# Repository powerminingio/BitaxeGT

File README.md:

# Bitaxe Gamma Turbo

Bitaxe Gamma Turbo is a dual BM1370 Open Source Bitcoin miner using [esp-miner](https://github.com/bitaxeorg/esp-miner). This project aims to provide a high-performance, energy-efficient Bitcoin mining solution using modern ASIC hardware.

## Version

The first release of the Bitaxe Gamma Turbo (GT) marks the version 801.

Major improvements over the version 800xxx are changes in the selected components and refitting components and headers on the PCB.

## Features

- Dual BM1370 ASIC
- Dual TPS546*
- Improved Mounting Hole selection
- 12V BAP
- EMC2103

The Bitaxe Gamma Turbo is the first iteration of a dual ASIC chip variant and marks the first point of multi-chip devices with modern ASIC hardware.

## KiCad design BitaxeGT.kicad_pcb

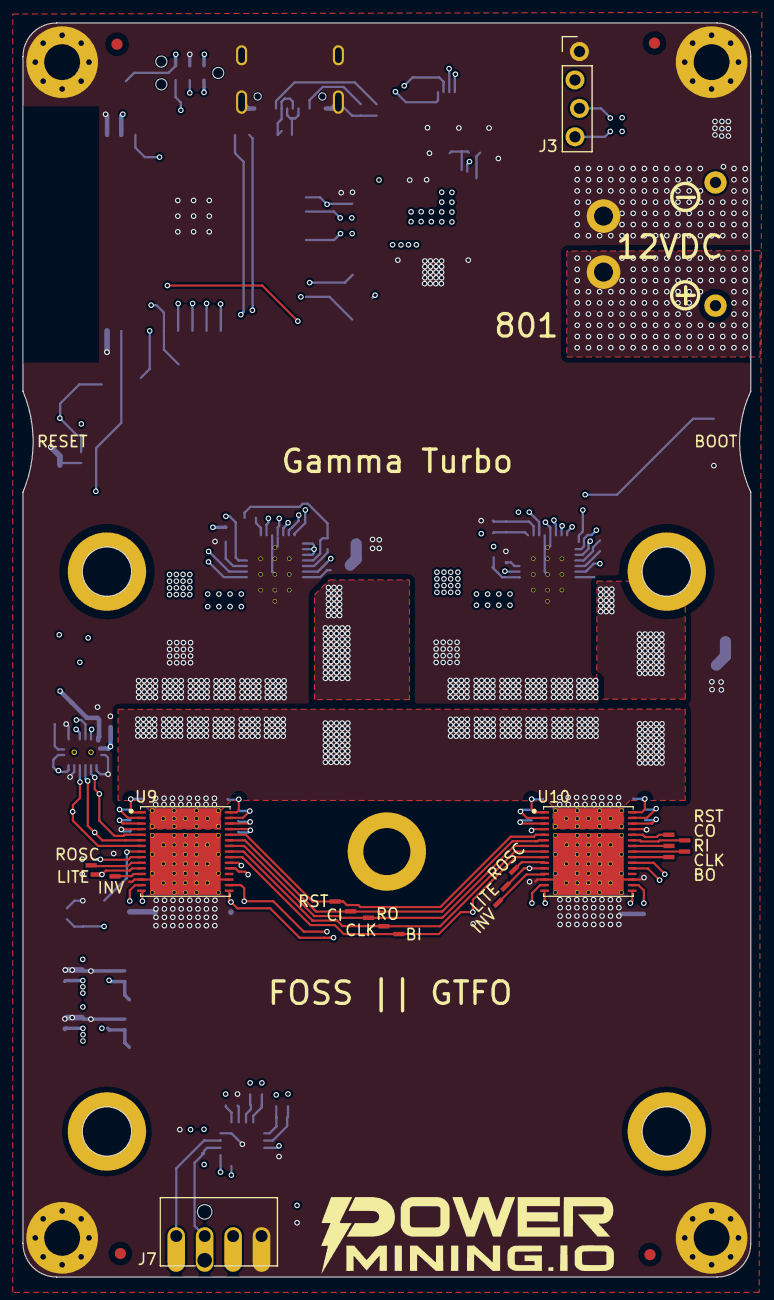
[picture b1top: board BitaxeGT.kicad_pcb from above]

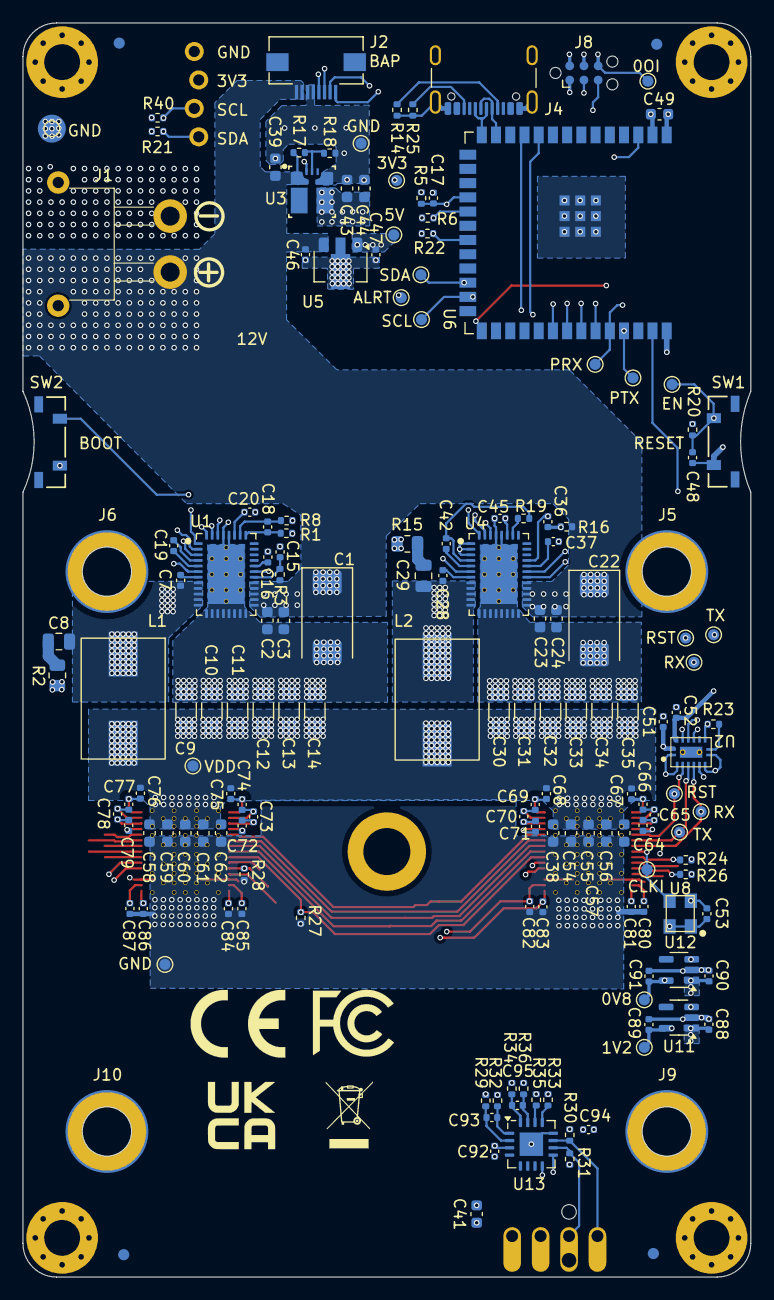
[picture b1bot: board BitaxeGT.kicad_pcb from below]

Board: 6 copper layers, 65.0 x 112.0 mm, 191 parts (163 on the bottom side), 98 nets.

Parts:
C1, C22: 33uF; CP_EIA-7343-31_Kemet-D
C2, C3, C23, C24, C38, C39, C41, C43, C44, C49, C54, C55, C56, C57, C58, C59, C60, C61, C62: 10uF; C_0603_1608Metric
C7, C17, C28, C51, C52, C53, C92, C94: 0.1uF; C_0402_1005Metric
C8, C29: 1000pF; C_0805_2012Metric
C9, C10, C11, C12, C13, C14, C30, C31, C32, C33, C34, C35: 100uF; C_1206_3216Metric
C15, C19, C36, C42, C46, C47, C64, C65, C66, C67, C68, C69, C70, C71, C72, C73, C74, C75, C76, C77, C78, C79, C80, C81, C82, C83, C84, C85, C86, C87, C88, C89, C90, C91: 1uF; C_0402_1005Metric
C16, C37: 4.7uF; C_0402_1005Metric
C18: 100pF; C_0402_1005Metric
C20, C45: 33pF; C_0402_1005Metric
C48: 12pF; C_0402_1005Metric
C93, C95: 470pF; C_0402_1005Metric
FID1, FID2, FID3, FID4: Fiducial; Fiducial_1mm_Mask2mm
H1, H2, H3, H4: MountingHole_Pad; MountingHole_3.2mm_M3_Pad_Via
HS1: Heatsink; Heatsink-5hole-BitaxeGT
J1: XT30; XT30PW-M
J2: Conn_01x08; FPC-SMD_P0.50-8P_FGS-XJ-H2.0
J3: Conn_01x04; PinHeader_1x04_P2.54mm_Vertical_shifted
J4: USB_C_Receptacle_USB2.0; USB_C_Receptacle_GCT_USB4105-xx-A
J5, J6, J9, J10: Screw_Terminal_01x01; WA-SMSI_9774005360
J7: Conn_01x04; 470531000
J8: TC2030-IDC; Tag-Connect_TC2030-IDC-NL_2x03_P1.27mm_Vertical
L1, L2: 300nH; SLC1175-271MEC_COC
Logo: 25mm; PM_logo_25mm
NT1, NT2: NetTie_2; NetTie-2_SMD_Pad0.2mmx1mm
R1, R8: 49.9; R_0402_1005Metric
R2, R15: 1; R_0805_2012Metric
R3, R16: 10; R_0402_1005Metric
R5, R6, R18, R19, R20, R24, R30, R33: 10k; R_0402_1005Metric
R14, R25: 5.1k; R_0402_1005Metric
R17, R23: 20k; R_0402_1005Metric
R21, R22, R40: 4.7k; R_0402_1005Metric
R26, R28: 1k; R_0402_1005Metric
R27: 2k; R_0402_1005Metric
R29, R32, R34, R36: 0; R_0402_1005Metric
R31: 5.6k; R_0402_1005Metric
R35: Rtrip; R_0402_1005Metric
SW1, SW2: SWITCH-SPST; SW_TL3330AF130QG_EWI
TP1, TP9: RST; TestPoint_Pad_1.0x0.4mm
TP2: CI; TestPoint_Pad_1.0x0.4mm
TP3: RO; TestPoint_Pad_1.0x0.4mm
TP4: CLKI; TestPoint_Pad_D1.0mm
TP5: BO; TestPoint_Pad_1.0x0.4mm
TP6, TP11: CLK; TestPoint_Pad_1.0x0.4mm
TP7: RI; TestPoint_Pad_1.0x0.4mm
TP8: CO; TestPoint_Pad_1.0x0.4mm
TP10, TP16: ROSC; TestPoint_Pad_1.0x0.4mm
TP12, TP20: LITE; TestPoint_Pad_1.0x0.4mm
TP13: BI; TestPoint_Pad_1.0x0.4mm
TP14, TP21: INV; TestPoint_Pad_1.0x0.4mm
TP15: VDD; TestPoint_Pad_D1.0mm
TP17, TP25, TP28: GND; TestPoint_Pad_D1.0mm
TP18: 1V2; TestPoint_Pad_D1.0mm
TP19: 0V8; TestPoint_Pad_D1.0mm
TP22: ALRT; TestPoint_Pad_D1.0mm
TP23: SDA; TestPoint_Pad_D1.0mm
TP24: SCL; TestPoint_Pad_D1.0mm
TP26, TP35: RST; TestPoint_Pad_D1.0mm
TP27: 5V; TestPoint_Pad_D1.0mm
TP29: EN; TestPoint_Pad_D1.0mm
TP30, TP37: TX; TestPoint_Pad_D1.0mm
TP31, TP38: RX; TestPoint_Pad_D1.0mm
TP32: PTX; TestPoint_Pad_D1.0mm
TP33: PRX; TestPoint_Pad_D1.0mm
TP34: 3V3; TestPoint_Pad_D1.0mm
TP36: IO0; TestPoint_Pad_D1.0mm
U1, U4: TPS546D24S; LQFN40-CLIP
U2: SN74AVC4T774; BQB0016A-MFG
U3: TPSM861253RDXR; TPSM863257RDX
U5: L78L05_SOT89; SOT-89-3
U6: ESP32-S3-WROOM-1
U8: 25MHz; SMD3225-4P
U9, U10: BM1370_mode1; BM1370_JB
U11: MCP1824T-1202E/OT; SOT-23-5
U12: MCP1824T-0802E; SOT-23-5
U13: EMC2103-2; QFN-16-1EP_4x4mm_P0.65mm_EP2.1x2.1mm

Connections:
/3V3: C43.1, C44.1, C49.1, C52.1, C92.1, J3.2, J8.2, R6.2, R20.2, R21.1, R22.1, R31.2, R33.2, R40.1, TP34.1, U2.15 (VCCB), U3.3 (VOUT), U3.7 (VOS), U6.2 (3V3), U13.3 (VDD)
/5V: C47.2, C88.2, C90.2, C94.1, R30.2, TP27.1, U5.1 (OUT), U11.1 (VIN), U11.3 (EN), U12.1 (VIN), U12.3 (EN)
/12V: C1.1, C2.1, C3.1, C22.1, C23.1, C24.1, C39.1, C41.1, C46.2, J1.1 (+V), J2.1, J2.2, J7.2, R3.1, R16.1, R17.2, U1.21 (PVIN), U1.22 (PVIN), U1.23 (PVIN), U1.24 (PVIN), U1.25 (PVIN), U3.1 (VIN), U4.21 (PVIN), U4.22 (PVIN), U4.23 (PVIN), U4.24 (PVIN), U4.25 (PVIN), U5.3 (IN)
/ASIC/0V8: C82.2, C85.2, C91.2, TP19.1, U9.17 (VDDIO_08_1), U10.14 (VDDIO_08_0), U12.5 (VOUT)
/ASIC/0V8_1: C80.2, U9.14 (VDDIO_08_0)
/ASIC/0V8_2: C87.2, U10.17 (VDDIO_08_1)
/ASIC/1V2: C51.1, C53.1, C83.2, C84.2, C89.2, TP18.1, U2.7 (DIR3), U2.8 (DIR4), U2.16 (VCCA), U8.1 (EN), U8.4 (VIN), U9.16 (VDDIO_12_1), U10.15 (VDDIO_12_0), U11.5 (VOUT)
/ASIC/1V2_1: C81.2, U9.15 (VDDIO_12_0)
/ASIC/1V2_2: C86.2, U10.16 (VDDIO_12_1)
/ASIC/BI: R24.2, U9.9 (BI)
/ASIC/CLKI: TP4.1, U8.3 (OUT), U9.8 (CLKI)
/ASIC/RST_1V2: TP35.1, U2.3 (A1), U9.5 (NRSTI)
/ASIC/RST_3V3: TP26.1, U2.14 (B1), U6.39 (GPIO1/TOUCH1/ADC1_CH0)
/ASIC/RX_1V2: TP38.1, U2.5 (A3), U9.7 (RO)
/ASIC/RX_3V3: TP31.1, U2.12 (B3), U6.11 (GPIO18/U1RXD/ADC2_CH7/CLK_OUT3)
/ASIC/TEMP1_N: R36.2, U9.21 (TEMP_N)
/ASIC/TEMP1_P: R34.2, U9.20 (TEMP_P)
/ASIC/TEMP2_N: R32.2, U10.21 (TEMP_N)
/ASIC/TEMP2_P: R29.2, U10.20 (TEMP_P)
/ASIC/TX_1V2: TP37.1, U2.4 (A2), U9.6 (CI)
/ASIC/TX_3V3: TP30.1, U2.13 (B2), U6.10 (GPIO17/U1TXD/ADC2_CH6)
/ESP32/EN: C48.1, J8.1, R20.1, SW1.2, TP29.1, U6.3 (EN)
/ESP32/IO0: J8.6, SW2.1, TP36.1, U6.27 (GPIO0/BOOT*)
/ESP32/PWR_EN: C17.1, R5.2, U1.27 (EN/UVLO), U4.27 (EN/UVLO), U6.18 (GPIO10/TOUCH10/ADC1_CH9/FSPICS0/FSPIIO4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)
/ESP32/P_RX: J8.5, TP33.1, U6.36 (U0RXD/GPIO44/CLK_OUT2)
/ESP32/P_TX: J8.3, TP32.1, U6.37 (U0TXD/GPIO43/CLK_OUT1)
/ESP32/SCL: J3.3, R40.2, TP24.1, U1.3 (PMB_CLK), U6.25 (GPIO48/SPICLK_N/SUBSPICLK_N_DIFF), U13.9 (SMCLK)
/ESP32/SDA: J3.4, R21.2, TP23.1, U1.2 (PMB_DATA), U6.24 (GPIO47/SPICLK_P/SUBSPICLK_P_DIFF), U13.8 (SMDATA)
/ESP32/SMB_ALRT: R22.2, TP22.1, U1.6 (SMB_ALRT), U6.21 (GPIO13/TOUCH13/ADC2_CH2/FSPIQ/FSPIIO7/S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)
/ESP32/USB_D+: J4.A6 (D+), J4.B6 (D+), U6.14 (GPIO20/U1CTS/ADC2_CH9/CLK_OUT1/USB_D+)
/ESP32/USB_D-: J4.A7 (D-), J4.B7 (D-), U6.13 (GPIO19/U1RTS/ADC2_CH8/CLK_OUT2/USB_D-)
/Power/AGND1: C15.1, C20.1, NT1.2, U1.37 (AGND)
/Power/AGND2: C36.1, C45.1, NT2.2, U4.1 (PGD), U4.2 (PMB_DATA), U4.3 (PMB_CLK), U4.6 (SMB_ALRT), U4.29 (MSEL2), U4.37 (AGND)
/Power/BCX_CLK: U1.39 (BCX_CLK), U4.39 (BCX_CLK)
/Power/BCX_DAT: U1.40 (BCX_DAT), U4.40 (BCX_DAT)
/Power/BP1v5_1: C19.1, U1.4 (BP1V5)
/Power/BP1v5_2: C42.1, R19.1, U4.4 (BP1V5)
/Power/PGOOD: R6.1, U1.1 (PGD), U6.19 (GPIO11/TOUCH11/ADC2_CH0/FSPID/FSPIIO5/S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)
/Power/SW1: C7.2, C8.1, L1.1, U1.8 (SW), U1.9 (SW), U1.10 (SW), U1.11 (SW), U1.12 (SW)
/Power/SW2: C28.2, C29.1, L2.1, U4.8 (SW), U4.9 (SW), U4.10 (SW), U4.11 (SW), U4.12 (SW)
/Power/SYNC: U1.38 (SYNC), U4.38 (SYNC)
/Power/V5reg_1: C16.2, U1.28 (VDD5)
/Power/V5reg_2: C37.2, U4.28 (VDD5)
/Power/VSHARE: C20.2, C45.2, U1.35 (VSHARE), U4.35 (VSHARE)
/VDD: C9.2, C10.2, C11.2, C12.2, C13.2, C14.2, C30.2, C31.2, C32.2, C33.2, C34.2, C35.2, C38.1, C54.1, C55.1, C56.1, C57.1, C58.1, C59.1, C60.1, C61.1, C62.1, C67.2, C68.1, C75.2, C76.1, L1.2, L2.2, R1.2, TP15.1, U9.31 (VDD), U10.31 (VDD)
/fan/FAN_PWM: J7.4, R30.1, U13.11 (FAN)
/fan/FAN_TACH: J7.3, R31.1, U13.10 (TACH)
GND: C1.2, C2.2, C3.2, C9.1, C10.1, C11.1, C12.1, C13.1, C14.1, C16.1, C17.2, C22.2, C23.2, C24.2, C30.1, C31.1, C32.1, C33.1, C34.1, C35.1, C37.1, C38.2, C39.2, C41.2, C43.2, C44.2, C46.1, C47.1, C48.2, C49.2, C51.2, C52.2, C53.2, C54.2, C55.2, C56.2, C57.2, C58.2, C59.2, C60.2, C61.2, C62.2, C64.1, C71.2, C72.1, C79.2, C80.1, C81.1, C82.1, C83.1, C84.1, C85.1, C86.1, C87.1, C88.1, C89.1, C90.1, C91.1, C92.2, C94.2, H1.1, H2.1, H3.1, H4.1, J1.2 (GND), J2.3, J2.4, J3.1, J4.A1 (GND), J4.B1 (GND), J4.S1 (SHIELD), J7.1, J8.4, NT1.1, NT2.1, R2.2, R5.1, R8.1, R14.1, R15.2, R18.1, R23.1, R24.1, R25.1, R26.1, R27.1, R28.1, R35.1, SW1.1, SW2.2, TP17.1, TP25.1, TP28.1, U1.13 (PGND), U1.14 (PGND), U1.15 (PGND), U1.16 (PGND), U1.17 (PGND), U1.18 (PGND), U1.19 (PGND), U1.20 (PGND), U1.36 (NC), U1.41 (PAD), U2.1 (DIR1), U2.2 (DIR2), U2.6 (A4), U2.10 (GND), U3.4 (PGND), U4.13 (PGND), U4.14 (PGND), U4.15 (PGND), U4.16 (PGND), U4.17 (PGND), U4.18 (PGND), U4.19 (PGND), U4.20 (PGND), U4.36 (NC), U4.41 (PAD), U5.2 (GND), U6.1 (GND), U6.40 (GND), U6.41 (GND), U8.2 (GND), U9.4 (VSS), U9.13 (PLL_VSS), U9.18 (VSS), U9.27 (VSS), U9.32 (VSS), U10.4 (VSS), U10.13 (PLL_VSS), U10.18 (VSS), U10.27 (VSS), U10.32 (VSS), U11.2 (GND), U12.2 (GND), U13.12 (GND), U13.17 (PAD)
unnamed: C8.2, R2.1
unnamed: C29.2, R15.1
unnamed: J2.5, U6.32 (MTCK/GPIO39/CLK_OUT3/SUBSPICS1)
unnamed: J2.6, U6.33 (MTDO/GPIO40/CLK_OUT2)
unnamed: J2.7, U6.34 (MTDI/GPIO41/CLK_OUT1)
unnamed: J2.8, U6.35 (MTMS/GPIO42)
unnamed: J4.A5 (CC1), R14.2
unnamed: J4.B5 (CC2), R25.2
unnamed: C15.2, R3.2, U1.26 (AVIN)
unnamed: C7.1, U1.7 (BOOT)
unnamed: C19.2, U1.5 (DRTN)
unnamed: C18.2, R8.2, U1.34 (GOSNS)
unnamed: C18.1, R1.1, U1.33 (VOSNS)
unnamed: R23.2, U2.9 (OE)
unnamed: R17.1, R18.2, U3.6 (EN)
unnamed: C36.2, R16.2, U4.26 (AVIN)
unnamed: C28.1, U4.7 (BOOT)
unnamed: C42.2, U4.5 (DRTN)
unnamed: R19.2, U4.34 (GOSNS)
unnamed: TP14.1, U9.12 (INV_CLKO)
unnamed: R26.2, TP12.1, U9.11 (LITE_PAD)
unnamed: TP10.1, U9.10 (ROSC_SEL)
unnamed: C64.2, C65.1, U9.3 (VDD1_0)
unnamed: C65.2, C66.1, U9.2 (VDD2_0)
unnamed: C66.2, C67.1, U9.1 (VDD3_0)
unnamed: R27.2, TP13.1, U9.22 (BO), U10.9 (BI)
unnamed: TP5.1, U10.22 (BO)
unnamed: TP2.1, U9.25 (CO), U10.6 (CI)
unnamed: TP11.1, U9.23 (CLKO), U10.8 (CLKI)
unnamed: TP6.1, U10.23 (CLKO)
unnamed: TP8.1, U10.25 (CO)
unnamed: TP21.1, U10.12 (INV_CLKO)
unnamed: R28.2, TP20.1, U10.11 (LITE_PAD)
unnamed: TP1.1, U9.26 (NRSTO), U10.5 (NRSTI)
unnamed: TP9.1, U10.26 (NRSTO)
unnamed: TP7.1, U10.24 (RI)
unnamed: TP3.1, U9.24 (RI), U10.7 (RO)
unnamed: TP16.1, U10.10 (ROSC_SEL)
unnamed: C70.2, C71.1, C72.2, C73.1, U9.28 (VDD1_1), U10.3 (VDD1_0)
unnamed: C78.2, C79.1, U10.28 (VDD1_1)
unnamed: C69.2, C70.1, C73.2, C74.1, U9.29 (VDD2_1), U10.2 (VDD2_0)
unnamed: C77.2, C78.1, U10.29 (VDD2_1)
unnamed: C68.2, C69.1, C74.2, C75.1, U9.30 (VDD3_1), U10.1 (VDD3_0)
unnamed: C76.2, C77.1, U10.30 (VDD3_1)
unnamed: C93.2, R32.1, U13.1 (DN1)
unnamed: C95.2, R36.1, U13.15 (DN2)
unnamed: C93.1, R29.1, U13.2 (DP1)
unnamed: C95.1, R34.1, U13.16 (DP2)
unnamed: R33.1, U13.13 (SHDN_SEL)
unnamed: R35.2, U13.14 (TRIP_SET)

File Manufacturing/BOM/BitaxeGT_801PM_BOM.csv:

"Qty","Reference","Value","PARTNO","Footprint","DK","Description"
"1","C18","100pF","CC0402JRNPO9BN101","Capacitor_SMD:C_0402_1005Metric","311-1024-1-ND","Unpolarized capacitor, small symbol"
"1","C48","12pF","CC0402JRNPO9BN120","Capacitor_SMD:C_0402_1005Metric","311-1016-1-ND","Unpolarized capacitor, small symbol"
"2","C1,C22","33uF","T495D336K025ATE300","Capacitor_Tantalum_SMD:CP_EIA-7343-31_Kemet-D","399-3882-1-ND","Polarized tantalum capacitor, small US symbol"
"6","C15,C19,C36,C42,C46,C47","1uF","TMK107B7105KA-T","Capacitor_SMD:C_0402_1005Metric","587-2984-1-ND","Unpolarized capacitor, small symbol"
"2","C16,C37","4.7uF","GRM155R61A475MEAAD","Capacitor_SMD:C_0402_1005Metric","490-14306-1-ND","Unpolarized capacitor, small symbol"
"19","C2,C3,C23,C24,C38,C39,C41,C43,C44,C49,C54,C55,C56,C57,C58,C59,C60,C61,C62","10uF","GRM188R61E106KA73D","Capacitor_SMD:C_0603_1608Metric","490-18214-1-ND","Unpolarized capacitor, small symbol"
"2","C20,C45","33pF","KGM05ACG1E330JH","Capacitor_SMD:C_0402_1005Metric","478-KGM05ACG1E330JHCT-ND","Unpolarized capacitor, small symbol"
"28","C64,C65,C66,C67,C68,C69,C70,C71,C72,C73,C74,C75,C76,C77,C78,C79,C80,C81,C82,C83,C84,C85,C86,C87,C88,C89,C90,C91","1uF","EMK105BJ105MV-F","Capacitor_SMD:C_0402_1005Metric","587-5514-1-ND","Unpolarized capacitor, small symbol"
"8","C7,C17,C28,C51,C52,C53,C92,C94","0.1uF","KGM05AR71C104KH","Capacitor_SMD:C_0402_1005Metric","478-KGM05AR71C104KHCT-ND","Unpolarized capacitor, small symbol"
"2","C8,C29","1000pF","CC0805KRX7R9BB102","Capacitor_SMD:C_0805_2012Metric","311-1127-1-ND","Unpolarized capacitor, small symbol"
"12","C9,C10,C11,C12,C13,C14,C30,C31,C32,C33,C34,C35","100uF","CL31A107MQHNNNE","Capacitor_SMD:C_1206_3216Metric","1276-1782-1-ND","Unpolarized capacitor, small symbol"
"2","C93,C95","470pF","GRM1555C1H471JA01D","Capacitor_SMD:C_0402_1005Metric","490-1297-1-ND","Unpolarized capacitor, small symbol"
"1","J1","XT30","XT30PW-M","bitaxe:XT30PW-M","~",""
"1","J2","Conn_01x08","FFC2B35-08-T","bitaxe:FPC-SMD_P0.50-8P_FGS-XJ-H2.0","2073-FFC2B35-08-TCT-ND",""
"1","J4","USB_C_Receptacle_USB2.0","USB4105-GF-A","bitaxe:USB_C_Receptacle_GCT_USB4105-xx-A","2073-USB4105-GF-ACT-ND","USB 2.0-only Type-C Receptacle connector"
"1","J7","Conn_01x04","0470531000","bitaxe:470531000","WM4330-ND","Generic connector, single row, 01x04, script generated (kicad-library-utils/schlib/autogen/connector/)"
"4","J5,J6,J9,J10","Screw_Terminal_01x01","9774005360R","bitaxe:WA-SMSI_9774005360","","WA-SMSI SMT STEEL SPACER M3 thread"
"2","L1,L2","300nH","SLC1175-271MEC","bitaxe:SLC1175-271MEC_COC","","Inductor"
"1","R27","2k","RT0402BRD072KL","Resistor_SMD:R_0402_1005Metric","YAG2303CT-ND","Resistor, small US symbol"
"1","R31","5.6k","RC0402FR-075K6L","Resistor_SMD:R_0402_1005Metric","311-5.6KLRCT-ND","Resistor, small US symbol"
"2","R1,R8","49.9","RC0402FR-0749R9L","Resistor_SMD:R_0402_1005Metric","311-49.9LRCT-ND","Resistor, small US symbol"
"2","R14,R25","5.1k","RMCF0402JT5K10","Resistor_SMD:R_0402_1005Metric","RMCF0402JT5K10CT-ND",""
"2","R17,R23","20k","RC0402FR-0720KL","Resistor_SMD:R_0402_1005Metric","311-20.0KLRCT-ND","Resistor, small US symbol"
"2","R2,R15","1","ESR10EZPJ1R0","Resistor_SMD:R_0805_2012Metric","RHM1KTR-ND","Resistor, small US symbol"
"3","R21,R22,R40","4.7k","RC0402JR-074K7L","Resistor_SMD:R_0402_1005Metric","311-4.7KJRCT-ND","Resistor, small US symbol"
"2","R26,R28","1k","RC0402FR-071KL","Resistor_SMD:R_0402_1005Metric","311-1.00KLRCT-ND","Resistor, small US symbol"
"4","R29,R32,R34,R36","0","RC0402JR-070RL","Resistor_SMD:R_0402_1005Metric","311-0.0JRCT-ND","Resistor, small US symbol"
"2","R3,R16","10","RC0402FR-0710RL","Resistor_SMD:R_0402_1005Metric","311-10.0LRCT-ND","Resistor, small US symbol"
"8","R5,R6,R18,R19,R20,R24,R30,R33","10k","RC0402JR-0710KL","Resistor_SMD:R_0402_1005Metric","311-10KJRCT-ND","Resistor, small US symbol"
"2","SW1,SW2","SWITCH-SPST","TL3330AF130QG","bitaxe:SW_TL3330AF130QG_EWI","EG4388CT-ND",""
"1","U2","SN74AVC4T774","SN74AXC4T774BQBR","bitaxe:BQB0016A-MFG","296-SN74AXC4T774BQBRCT-ND",""
"1","U3","TPSM861253RDXR","TPSM861253RDXR","bitaxe:TPSM863257RDX","296-TPSM861253RDXRCT-ND","17V input, stepdown, 3.3V 1A output, DC/DC converter, 7-PowerFQFN Module"
"1","U5","L78L05_SOT89","UA78L05ACPK","Package_TO_SOT_SMD:SOT-89-3","296-11118-1-ND","Positive 100mA 30V Linear Regulator, Fixed Output 5V, SOT-89"
"1","U6","ESP32-S3-WROOM-1","ESP32-S3-WROOM-1-N16R8","bitaxe:ESP32-S3-WROOM-1","1965-ESP32-S3-WROOM-1-N16R8CT-ND","2.4 GHz WiFi (802.11 b/g/n) and Bluetooth ® 5 (LE) module Built around ESP32S3 series of SoCs, Xtensa ® dualcore 32bit LX7 microprocessor Flash up to 16 MB, PSRAM up to 8 MB 36 GPIOs, rich set of peripherals Onboard PCB antenna"
"1","U8","25MHz","SX3M25.000E20F30THN","bitaxe:SMD3225-4P","5852-SX3M25.000E20F30THNTR-ND",""
"1","U11","MCP1824T-1202E/OT","MCP1824T-1202E/OT","Package_TO_SOT_SMD:SOT-23-5","MCP1824T-1202E/OTCT-ND",""
"1","U12","MCP1824T-0802E","MCP1824T-0802E/OT","Package_TO_SOT_SMD:SOT-23-5","MCP1824T-0802E/OTCT-ND",""
"1","U13","EMC2103-2","EMC2103-4-AP-TR","Package_DFN_QFN:QFN-16-1EP_4x4mm_P0.65mm_EP2.1x2.1mm","150-EMC2103-4-AP-CT-ND",""
"2","U1,U4","TPS546D24S","TPS546D24SRVFR","bitaxe:LQFN40-CLIP","296-TPS546D24SRVFRCT-ND",""
"2","U9,U10","BM1370_mode1","","bitaxe:BM1370","",""

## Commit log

2026-02-09 Various changes in PCB
    - Updated BM1370 footprint
    - Added treaded spacers for heatsink
    - Added component references on silkscreen
    - Added PM logo
    - Added BITAXE logo in solder mask expansion level
    - Exported BOM and Gerber files
2026-02-09 Changes in README.md
2026-02-09 ASIC.sch update in BM footprint
